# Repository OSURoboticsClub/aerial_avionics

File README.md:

Aerial Avionics
===============
_Hardware design files for aerial team avionics_

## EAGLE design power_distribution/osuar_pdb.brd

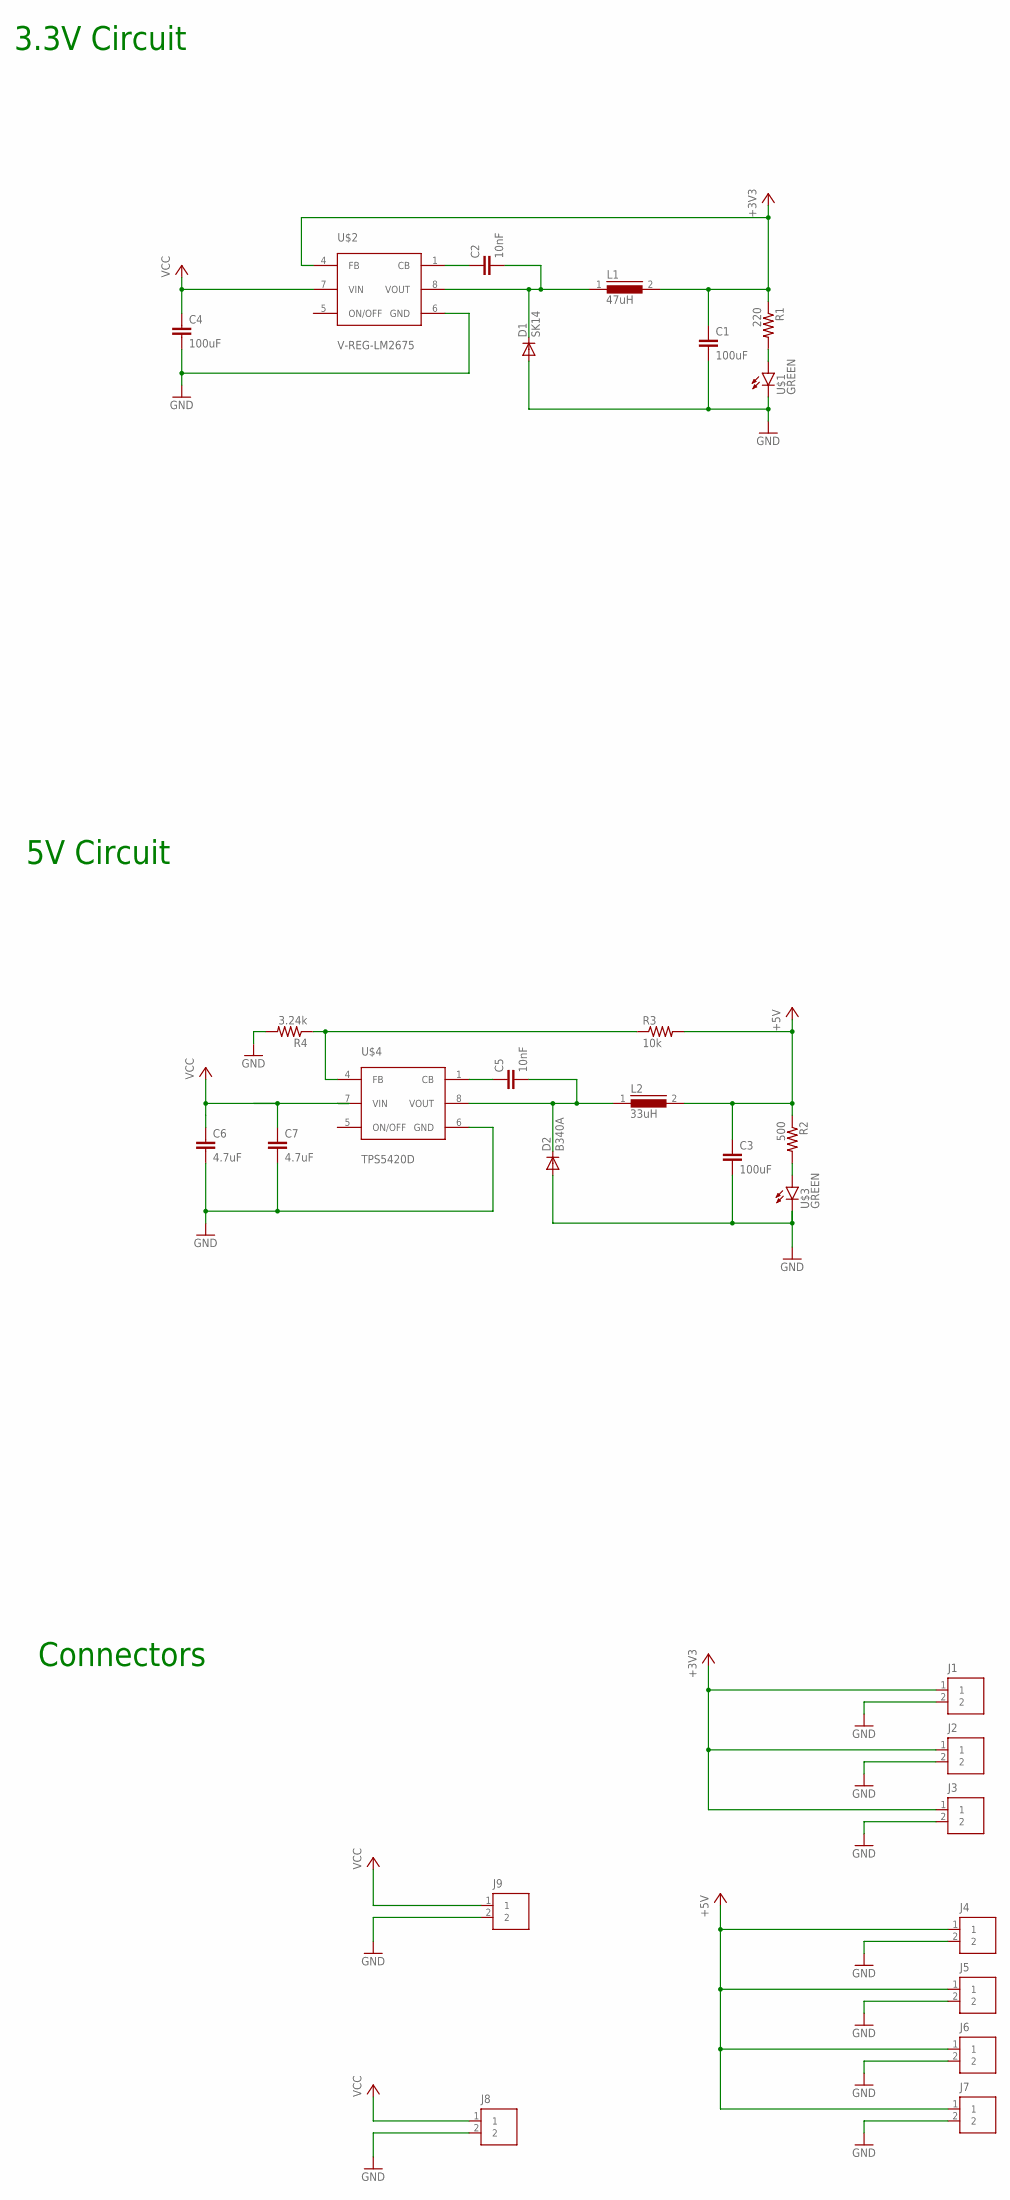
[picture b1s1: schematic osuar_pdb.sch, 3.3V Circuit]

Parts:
C1, C3, C4: 100uF; 0805
C2, C5: 10nF; 0603
C6, C7: 4.7uF; 0805
D1: SK14; DO214AA
D2: B340A; DO214AA
J1, J2, J3, J4, J5, J6, J7, J8, J9: M02; MOLEX-2MM-MICROLATCH-2POS-RA
L1: 47uH; DR125
L2: 33uH; DR125
R1: 220; 0603
R2: 500; 0603
R3: 10k; 0603
R4: 3.24k; 0603
U$1, U$3: GREEN; LED-0603
U$2: V-REG-LM2675; SOIC8
U$4: TPS5420D; SOIC8

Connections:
+3V3: C1.2, J1.1, J2.1, J3.1, L1.2, R1.1, U$2.4 (FB)
+5V: C3.2, J4.1, J5.1, J6.1, J7.1, L2.2, R2.1, R3.2
GND: C1.1, C3.1, C4.1, C6.1, C7.1, D1.A, D2.A, J1.2, J2.2, J3.2, J4.2, J5.2, J6.2, J7.2, J8.2, J9.2, R4.2, U$1.C, U$2.6 (GND), U$3.C, U$4.6 (GND)
unnamed: C5.1, D2.C, L2.1, U$4.8 (VOUT)
unnamed: C2.2, U$2.1 (CB)
unnamed: R1.2, U$1.A
unnamed: C5.2, U$4.1 (CB)
unnamed: C2.1, D1.C, L1.1, U$2.8 (VOUT)
unnamed: R2.2, U$3.A
unnamed: R3.1, R4.1, U$4.4 (FB)
VCC: C4.2, C6.2, C7.2, J8.1, J9.1, U$2.7 (VIN), U$4.7 (VIN)

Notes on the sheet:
3.3V Circuit
5V Circuit
Connectors

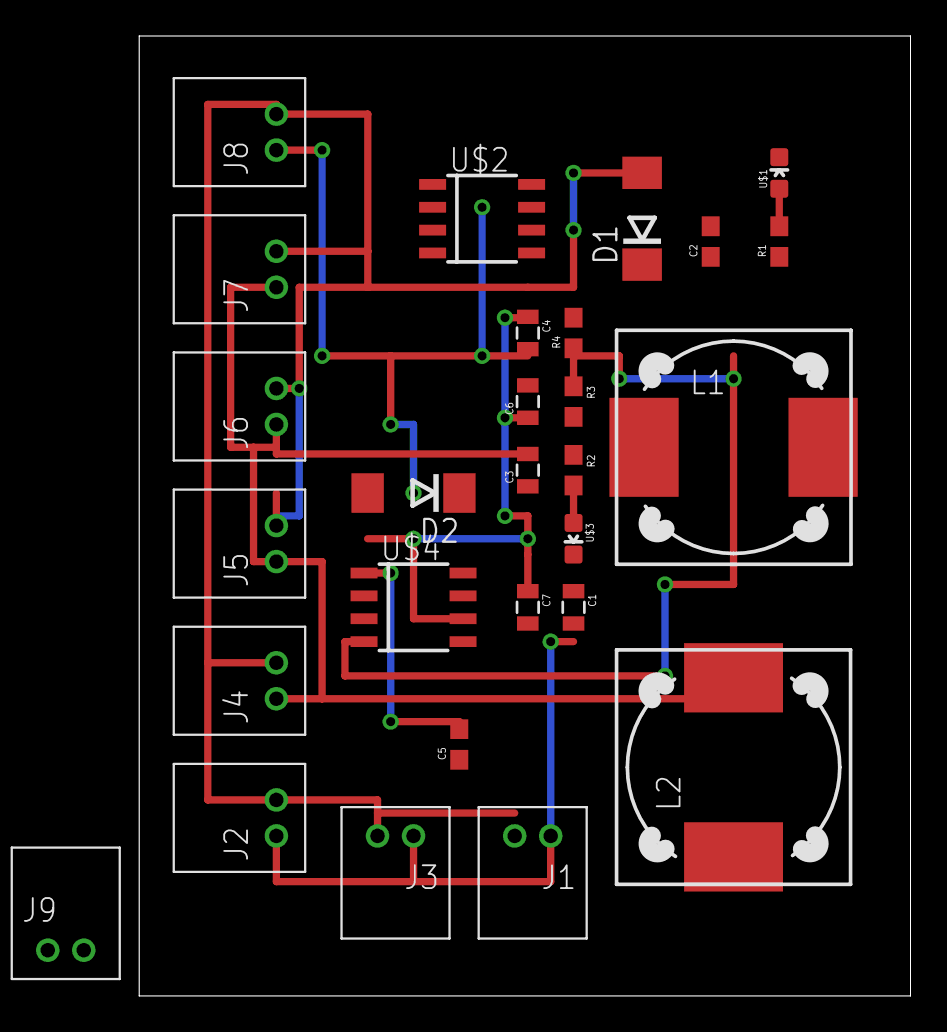
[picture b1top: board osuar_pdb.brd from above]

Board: 2 copper layers, 42.9 x 53.3 mm, 28 parts (0 on the bottom side), 11 nets.

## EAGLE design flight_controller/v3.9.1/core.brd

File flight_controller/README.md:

Aerial Flight Controller
========================
_Flight control board_

v3.9
----
_In fabrication_

Complete redesign with new microcontroller pin configuration. Significant
additions include the following:

  * MS5611 barometer
  * MPU-9250 9DoF sensor in place of MPU-6000
  * MicroSD card reader
  * Full-speed USB
  * More TIM channels and UART buses
  * Killswitch BJTs replaced with MOSFETs, and more of 'em
  * External SPI and I2C buses
  * Molex MicroLatch 2mm connectors in place of bulkier sherlock
  * Reverse voltage protection and TVS on 5V input
  * External crystal oscillator on STM32F4
  * Blinding status LED

This will be a development version with many debug pads and a rather open
layout for easier troubleshooting.

v3.4
----
2014 competition year. Separated IMU to daughter board to resolve board flex
issue. Added 2mm female headers to board for XBee.

v3.0
----
2013 competition year. Designed to work with and share form factor as Odroid
X2. Big issue with board flex affecting MEMS IMU.

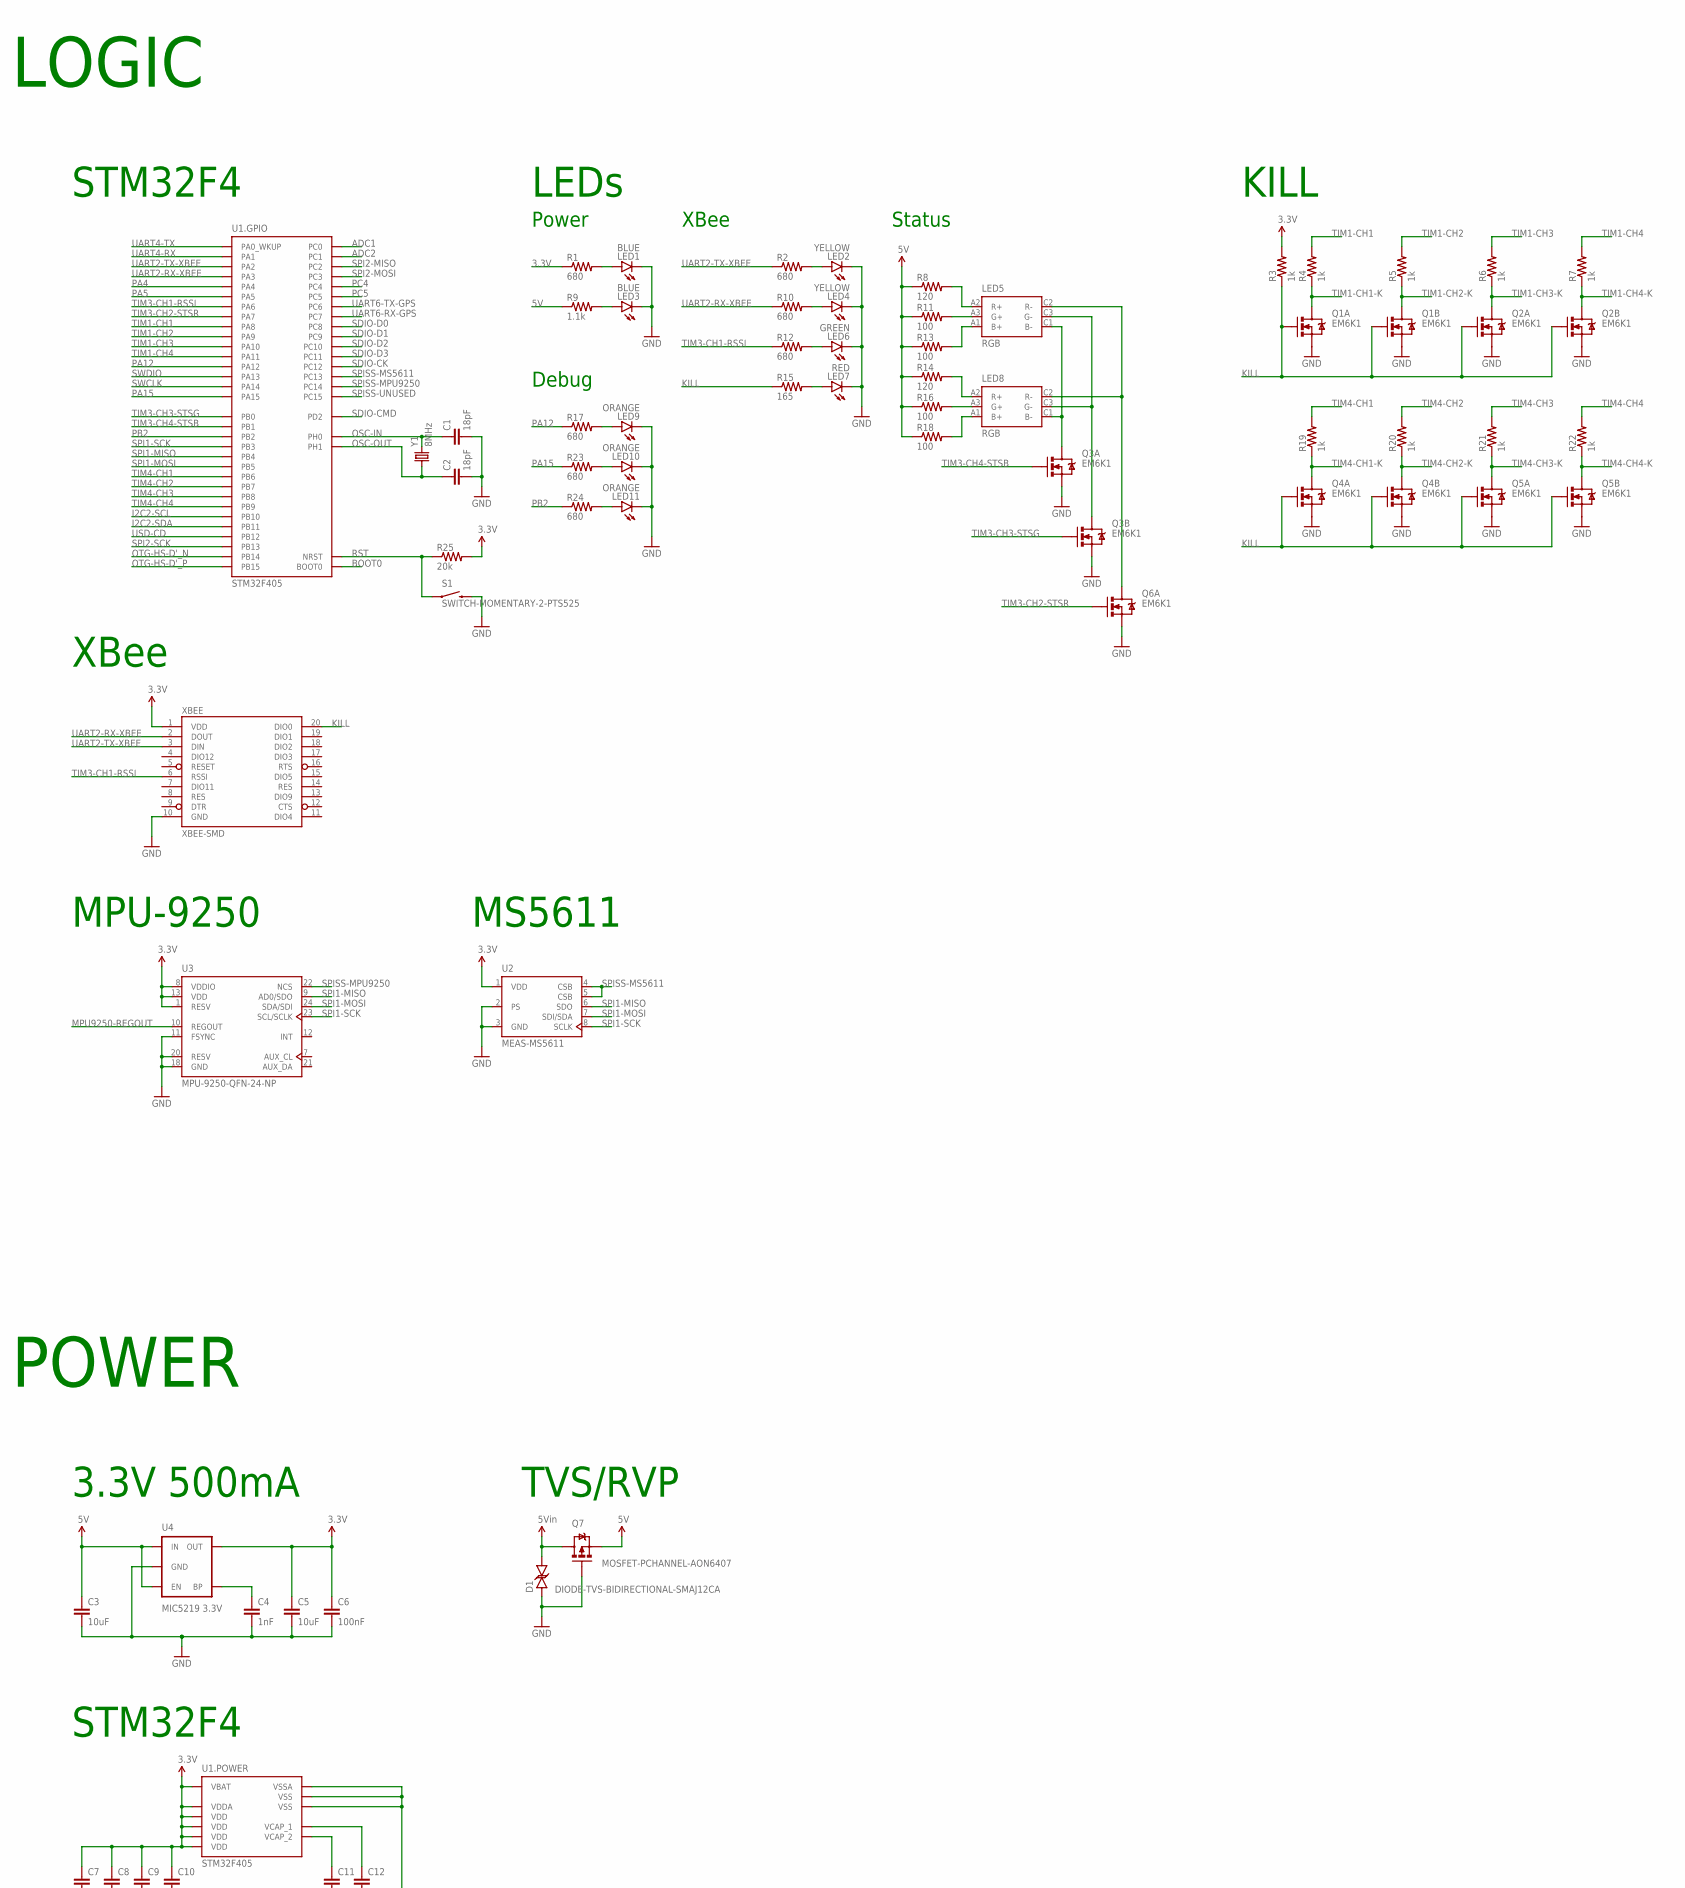
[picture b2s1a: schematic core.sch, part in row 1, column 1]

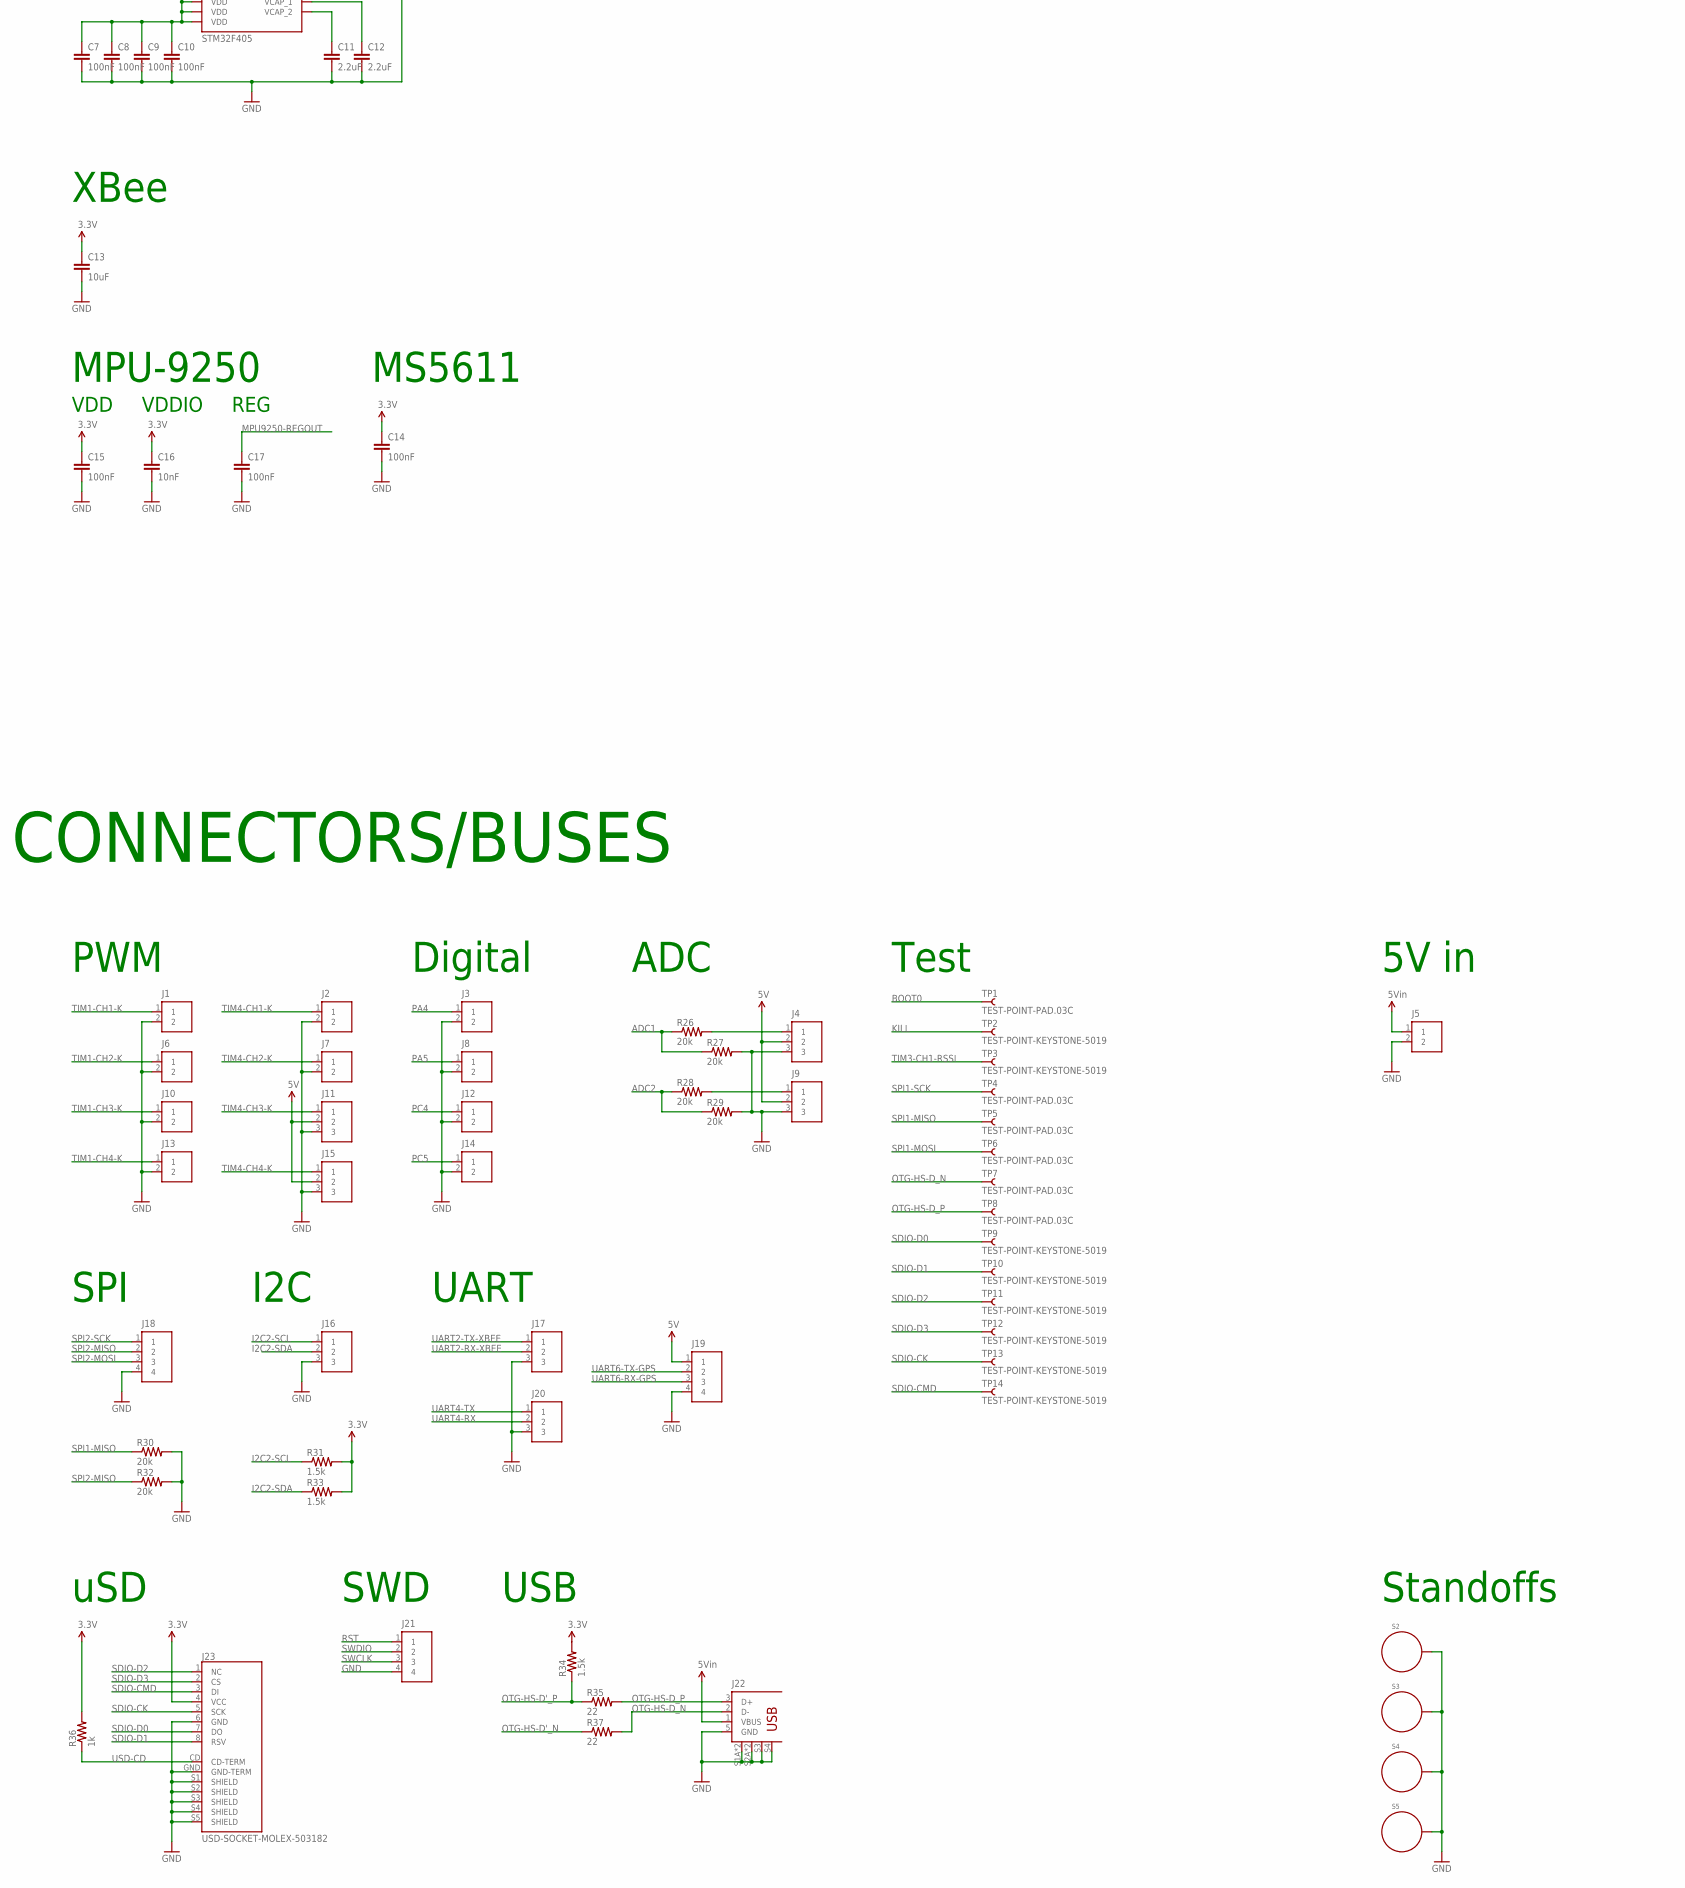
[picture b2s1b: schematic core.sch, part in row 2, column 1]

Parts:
C1, C2: 18pF; 0603
C3, C5, C13: 10uF; 0805
C4: 1nF; 0603
C6, C7, C8, C9, C10, C14, C15, C17: 100nF; 0603
C11, C12: 2.2uF; 0603
C16: 10nF; 0603
D1: DIODE-TVS-BIDIRECTIONAL-SMAJ12CA; SMAJ
J1, J2, J3, J5, J6, J7, J8, J10, J12, J13, J14: M02; MOLEX-2MM-MICROLATCH-2POS-RA
J4, J9, J11, J15, J16, J17, J20: M03; MOLEX-2MM-MICROLATCH-3POS-RA
J18, J19, J21: M04; MOLEX-2MM-MICROLATCH-4POS-RA
J22: USB+SHIELD-MICROB-SMD-MOLEX; USB-MICROB-SMD-MOLEX
J23: USD-SOCKET-MOLEX-503182; USD-SOCKET-PP-MOLEX-503182
LED1, LED3: BLUE; LED-0603
LED2, LED4: YELLOW; LED-0603
LED5, LED8: RGB; PLCC-6
LED6: GREEN; LED-0603
LED7: RED; LED-0603
LED9, LED10, LED11: ORANGE; LED-0603
Q1, Q2, Q3, Q4, Q5, Q6: EM6K1; SOT-666
Q7: MOSFET-PCHANNEL-AON6407; DFN5X6
R1, R2, R10, R12, R17, R23, R24: 680; 0603
R3, R4, R5, R6, R7, R19, R20, R21, R22, R36: 1k; 0603
R8, R14: 120; 0603
R9: 1.1k; 0603
R11, R13, R16, R18: 100; 0603
R15: 165; 0603
R25, R26, R27, R28, R29, R30, R32: 20k; 0603
R31, R33, R34: 1.5k; 0603
R35, R37: 22; 0603
S1: SWITCH-MOMENTARY-2-PTS525; TACTILE-SWITCH-SMD
S2, S3, S4, S5: STANDOFF_ELECTRICAL-#4; STANDOFF-ELECTRICAL-#4
TP1, TP4, TP5, TP6, TP7, TP8: TEST-POINT-PAD.03C; PAD-.03C
TP2, TP3, TP9, TP10, TP11, TP12, TP13, TP14: TEST-POINT-KEYSTONE-5019; PAD.15X.08
U1: STM32F405; LQFP-64-STM32F405
U2: MEAS-MS5611
U3: MPU-9250-QFN-24-NP; QFN-24-NP-3X3MM
U4: MIC5219 3.3V; SOT23-5
XBEE: XBEE-SMD
Y1: 8MHz; CX532

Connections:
3.3V: C5.2, C6.2, C7.2, C8.2, C9.2, C10.2, C13.2, C14.2, C15.2, C16.2, J23.4 (VCC), R1.1, R3.2, R25.2, R31.2, R33.2, R34.2, R36.2, U1.1 (VBAT), U1.13 (VDDA), U1.19 (VDD), U1.32 (VDD), U1.48 (VDD), U1.64 (VDD), U2.1 (VDD), U3.1 (RESV), U3.8 (VDDIO), U3.13 (VDD), U4.5 (OUT), XBEE.1 (VDD)
5V: C3.2, J4.2, J9.2, J11.2, J15.2, J19.1, Q7.1 (S), Q7.2 (S), Q7.3 (S), R8.1, R9.1, R11.1, R13.1, R14.1, R16.1, R18.1, U4.1 (IN), U4.3 (EN)
ADC1: R26.1, R27.1, U1.8 (PC0)
ADC1-IN: J4.1, R26.2
ADC2: R28.1, R29.1, U1.9 (PC1)
ADC2-IN: J9.1, R28.2
BOOT0: TP1.1, U1.60 (BOOT0)
F4-VCAP-1: C11.2, U1.47 (VCAP_2)
F4-VCAP-2: C12.2, U1.31 (VCAP_1)
GND: C1.1, C2.1, C3.1, C4.1, C5.1, C6.1, C7.1, C8.1, C9.1, C10.1, C11.1, C12.1, C13.1, C14.1, C15.1, C16.1, C17.1, D1.A (1), J1.2, J2.2, J3.2, J4.3, J5.2, J6.2, J7.2, J8.2, J9.3, J10.2, J11.3, J12.2, J13.2, J14.2, J15.3, J16.3, J17.3, J18.4, J19.4, J20.3, J21.4, J22.5 (GND), J22.S1A (S1), J22.S1B (S1), J22.S2A (S2), J22.S2B (S2), J22.S3, J22.S4, J23.6 (GND), J23.GND (GND-TERM), J23.S1 (SHIELD), J23.S2 (SHIELD), J23.S3 (SHIELD), J23.S4 (SHIELD), J23.S5 (SHIELD), LED1.C, LED2.C, LED3.C, LED4.C, LED6.C, LED7.C, LED9.C, LED10.C, LED11.C, Q1.1 (S), Q1.4 (S), Q2.1 (S), Q2.4 (S), Q3.1 (S), Q3.4 (S), Q4.1 (S), Q4.4 (S), Q5.1 (S), Q5.4 (S), Q6.1 (S), Q7.4 (G), R27.2, R29.2, R30.2, R32.2, S1.3 (2), S1.4 (2), S2.P1, S3.P1, S4.P1, S5.P1, U1.12 (VSSA), U1.18 (VSS), U1.63 (VSS), U2.2 (PS), U2.3 (GND), U3.11 (FSYNC), U3.18 (GND), U3.20 (RESV), U4.2 (GND), XBEE.10 (GND)
I2C2-SCL: J16.1, R31.1, U1.29 (PB10)
I2C2-SDA: J16.2, R33.1, U1.30 (PB11)
KILL: Q1.2 (G), Q1.5 (G), Q2.2 (G), Q2.5 (G), Q4.2 (G), Q4.5 (G), Q5.2 (G), Q5.5 (G), R3.1, R15.1, TP2.1, XBEE.20 (DIO0)
MIC-BP: C4.2, U4.4 (BP)
MPU9250-REGOUT: C17.2, U3.10 (REGOUT)
unnamed: LED9.A, R17.2
unnamed: LED10.A, R23.2
unnamed: LED11.A, R24.2
unnamed: LED6.A, R12.2
unnamed: LED7.A, R15.2
unnamed: LED2.A, R2.2
unnamed: LED4.A, R10.2
unnamed: LED1.A, R1.2
unnamed: LED3.A, R9.2
OSC-IN: C1.2, U1.5 (PH0), Y1.2
OSC-OUT: C2.2, U1.6 (PH1), Y1.1
OTG-HS-D'_N: R37.1, U1.35 (PB14)
OTG-HS-D'_P: R34.1, R35.1, U1.36 (PB15)
OTG-HS-D_N: J22.2 (D-), R37.2, TP7.1
OTG-HS-D_P: J22.3 (D+), R35.2, TP8.1
PA4: J3.1, U1.20 (PA4)
PA5: J8.1, U1.21 (PA5)
PA12: R17.1, U1.45 (PA12)
PA15: R23.1, U1.50 (PA15)
PB2: R24.1, U1.28 (PB2)
PC4: J12.1, U1.24 (PC4)
PC5: J14.1, U1.25 (PC5)
RST: J21.1, R25.1, S1.1, S1.2 (1), U1.7 (NRST)
SDIO-CK: J23.5 (SCK), TP13.1, U1.53 (PC12)
SDIO-CMD: J23.3 (DI), TP14.1, U1.54 (PD2)
SDIO-D0: J23.7 (DO), TP9.1, U1.39 (PC8)
SDIO-D1: J23.8 (RSV), TP10.1, U1.40 (PC9)
SDIO-D2: J23.1 (NC), TP11.1, U1.51 (PC10)
SDIO-D3: J23.2 (CS), TP12.1, U1.52 (PC11)
SPI1-MISO: R30.1, TP5.1, U1.56 (PB4), U2.6 (SDO), U3.9 (AD0/SDO)
SPI1-MOSI: TP6.1, U1.57 (PB5), U2.7 (SDI/SDA), U3.24 (SDA/SDI)
SPI1-SCK: TP4.1, U1.55 (PB3), U2.8 (SCLK), U3.23 (SCL/SCLK)
SPI2-MISO: J18.2, R32.1, U1.10 (PC2)
SPI2-MOSI: J18.3, U1.11 (PC3)
SPI2-SCK: J18.1, U1.34 (PB13)
SPISS-MPU9250: U1.3 (PC14), U3.22 (NCS)
SPISS-MS5611: U1.2 (PC13), U2.4 (CSB), U2.5 (CSB)
SPISS-UNUSED: U1.4 (PC15)
STSB1+: LED5.A1 (B+), R13.2
STSB2+: LED8.A1 (B+), R18.2
STSB-: LED5.C1 (B-), LED8.C1 (B-), Q3.6 (D)
STSG1+: LED5.A3 (G+), R11.2
STSG2+: LED8.A3 (G+), R16.2
STSG-: LED5.C3 (G-), LED8.C3 (G-), Q3.3 (D)
STSR1+: LED5.A2 (R+), R8.2
STSR2+: LED8.A2 (R+), R14.2
STSR-: LED5.C2 (R-), LED8.C2 (R-), Q6.6 (D)
SWCLK: J21.3, U1.49 (PA14)
SWDIO: J21.2, U1.46 (PA13)
TIM1-CH1: R4.2, U1.41 (PA8)
TIM1-CH1-K: J1.1, Q1.6 (D), R4.1
TIM1-CH2: R5.2, U1.42 (PA9)
TIM1-CH2-K: J6.1, Q1.3 (D), R5.1
TIM1-CH3: R6.2, U1.43 (PA10)
TIM1-CH3-K: J10.1, Q2.6 (D), R6.1
TIM1-CH4: R7.2, U1.44 (PA11)
TIM1-CH4-K: J13.1, Q2.3 (D), R7.1
TIM3-CH1-RSSI: R12.1, TP3.1, U1.22 (PA6), XBEE.6 (RSSI)
TIM3-CH2-STSR: Q6.2 (G), U1.23 (PA7)
TIM3-CH3-STSG: Q3.5 (G), U1.26 (PB0)
TIM3-CH4-STSB: Q3.2 (G), U1.27 (PB1)
TIM4-CH1: R19.2, U1.58 (PB6)
TIM4-CH1-K: J2.1, Q4.6 (D), R19.1
TIM4-CH2: R20.2, U1.59 (PB7)
TIM4-CH2-K: J7.1, Q4.3 (D), R20.1
TIM4-CH3: R21.2, U1.61 (PB8)
TIM4-CH3-K: J11.1, Q5.6 (D), R21.1
TIM4-CH4: R22.2, U1.62 (PB9)
TIM4-CH4-K: J15.1, Q5.3 (D), R22.1
UART2-RX-XBEE: J17.2, R10.1, U1.17 (PA3), XBEE.2 (DOUT)
UART2-TX-XBEE: J17.1, R2.1, U1.16 (PA2), XBEE.3 (DIN)
UART4-RX: J20.2, U1.15 (PA1)
UART4-TX: J20.1, U1.14 (PA0_WKUP)
UART6-RX-GPS: J19.3, U1.38 (PC7)
UART6-TX-GPS: J19.2, U1.37 (PC6)
USD-CD: J23.CD (CD-TERM), R36.1, U1.33 (PB12)
VIN: D1.C (2), J5.1, J22.1 (VBUS), Q7.5 (D), Q7.6 (D), Q7.7 (D), Q7.8 (D), Q7.9 (D), Q7.10 (D)

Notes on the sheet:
3.3V 500mA
XBee
ADC
UART
PWM
SWD
KILL
STM32F4
LOGIC
POWER
USB
uSD
CONNECTORS/BUSES
LEDs
Debug
Power
MPU-9250
MS5611
SPI
I2C
Status
5V in
TVS/RVP
VDD
REG
VDDIO
Digital
Test
Standoffs

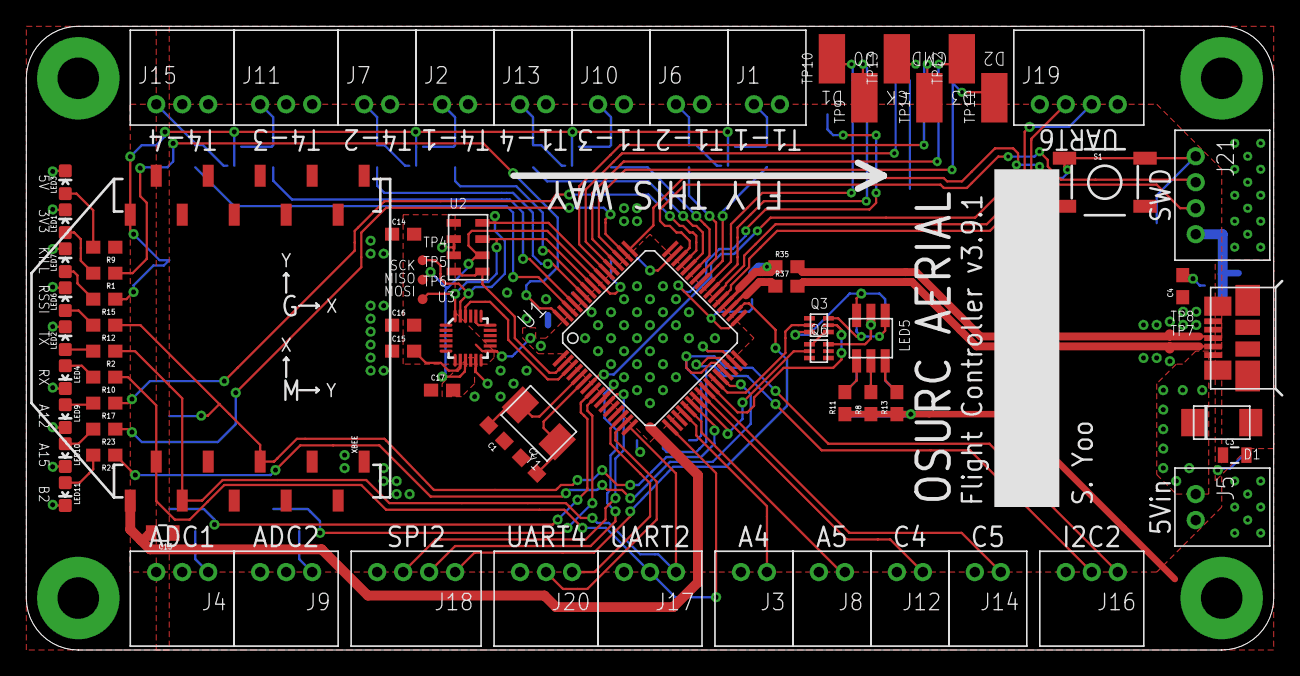
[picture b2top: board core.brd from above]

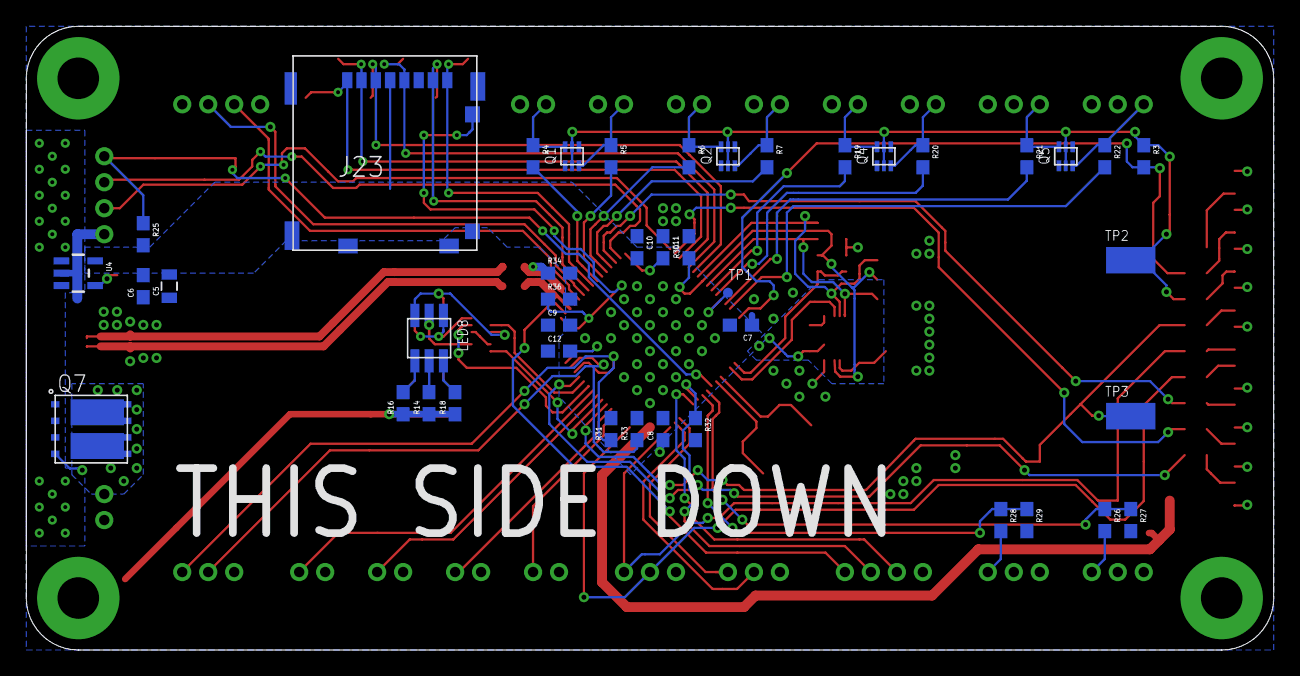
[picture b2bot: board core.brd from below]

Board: 2 copper layers, 96.0 x 48.0 mm, 121 parts (42 on the bottom side), 91 nets.

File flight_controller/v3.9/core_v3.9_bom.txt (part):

Partlist exported from /home/yoos/devel/aerial_avionics/flight_controller/core.sch at 1/13/15 10:14 PM

Part  Value                            Device                           Package                      Description                                                                                CDI_PN          DIGIKEY_PN     VALUE
C1    18pF                             CAP-18PF-50V-5%(0603)            0603                                                                                                                                    490-1409-1-ND  18pF
C2    18pF                             CAP-18PF-50V-5%(0603)            0603                                                                                                                                    490-1409-1-ND  18pF
C3    10uF                             CAP-10UF-10V-10%(0805)           0805                                                                                                                                    490-1709-1-ND  10uF
C4    1nF                              CAP-1NF-50V-10%(0603)            0603                                                                                                                                    490-1494-1-ND  1nF
C5    10uF                             CAP-10UF-10V-10%(0805)           0805                                                                                                                                    490-1709-1-ND  10uF
C6    100nF                            CAP-100NF-16V-10%(0603)          0603                                                                                                                                    490-1532-1-ND  100nF
C7    100nF                            CAP-100NF-16V-10%(0603)          0603                                                                                                                                    490-1532-1-ND  100nF
C8    100nF                            CAP-100NF-16V-10%(0603)          0603                                                                                                                                    490-1532-1-ND  100nF
C9    100nF                            CAP-100NF-16V-10%(0603)          0603                                                                                                                                    490-1532-1-ND  100nF
C10   100nF                            CAP-100NF-16V-10%(0603)          0603                                                                                                                                    490-1532-1-ND  100nF
C11   2.2uF                            CAP-2.2UF-10V-10%(0603)          0603                                                                                                                                    490-1545-1-ND  2.2uF
C12   2.2uF                            CAP-2.2UF-10V-10%(0603)          0603                                                                                                                                    490-1545-1-ND  2.2uF
C13   10uF                             CAP-10UF-10V-10%(0805)           0805                                                                                                                                    490-1709-1-ND  10uF
C14   100nF                            CAP-100NF-16V-10%(0603)          0603                                                                                                                                    490-1532-1-ND  100nF
C15   100nF                            CAP-100NF-16V-10%(0603)          0603                                                                                                                                    490-1532-1-ND  100nF
C16   10nF                             CAP-10NF-50V-10%(0603)           0603                                                                                                                                    490-1512-1-ND  10nF
C17   100nF                            CAP-100NF-16V-10%(0603)          0603                                                                                                                                    490-1532-1-ND  100nF
D1    DIODE-TVS-BIDIRECTIONAL-SMAJ12CA DIODE-TVS-BIDIRECTIONAL-SMAJ12CA SMAJ                         Generic bidirectional TVS diode.                                                                           SMAJ12CABCT-ND
J1    M02                              M02                              MOLEX-2MM-MICROLATCH-2POS-RA                                                                                                            WM18999-ND
J2    M02                              M02                              MOLEX-2MM-MICROLATCH-2POS-RA                                                                                                            WM18999-ND
J3    M02                              M02                              MOLEX-2MM-MICROLATCH-2POS-RA                                                                                                            WM18999-ND
J4    M03                              M03                              MOLEX-2MM-MICROLATCH-3POS-RA                                                                                                            WM19000-ND
J5    M02                              M02                              MOLEX-2MM-MICROLATCH-2POS-RA                                                                                                            WM18999-ND
J6    M02                              M02                              MOLEX-2MM-MICROLATCH-2POS-RA                                                                                                            WM18999-ND
J7    M02                              M02                              MOLEX-2MM-MICROLATCH-2POS-RA                                                                                                            WM18999-ND
J8    M02                              M02                              MOLEX-2MM-MICROLATCH-2POS-RA                                                                                                            WM18999-ND
J9    M03                              M03                              MOLEX-2MM-MICROLATCH-3POS-RA                                                                                                            WM19000-ND
J10   M02                              M02                              MOLEX-2MM-MICROLATCH-2POS-RA                                                                                                            WM18999-ND
J11   M03                              M03                              MOLEX-2MM-MICROLATCH-3POS-RA                                                                                                            WM19000-ND
J12   M02                              M02                              MOLEX-2MM-MICROLATCH-2POS-RA                                                                                                            WM18999-ND
J13   M02                              M02                              MOLEX-2MM-MICROLATCH-2POS-RA                                                                                                            WM18999-ND
J14   M02                              M02                              MOLEX-2MM-MICROLATCH-2POS-RA                                                                                                            WM18999-ND
J15   M03                              M03                              MOLEX-2MM-MICROLATCH-3POS-RA                                                                                                            WM19000-ND
J16   M03                              M03                              MOLEX-2MM-MICROLATCH-3POS-RA                                                                                                            WM19000-ND
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

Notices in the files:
parts and their libraries:
SparkFun-Aesthetics: Licensing: Creative Commons ShareAlike 4.0 International - https://creativecommons.org/licenses/by-sa/4.0
SparkFun-Sensors: Licensing: CC v3.0 Share-Alike You are welcome to use this library for commercial purposes.
